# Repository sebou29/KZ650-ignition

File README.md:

# KZ650-ignition
KZ650 ignition arduino nano

Arduino nano ignition for four stroke engine motorcycle (KZ650) 
Inspired by aepl and aecp
Optimized for kickstarter

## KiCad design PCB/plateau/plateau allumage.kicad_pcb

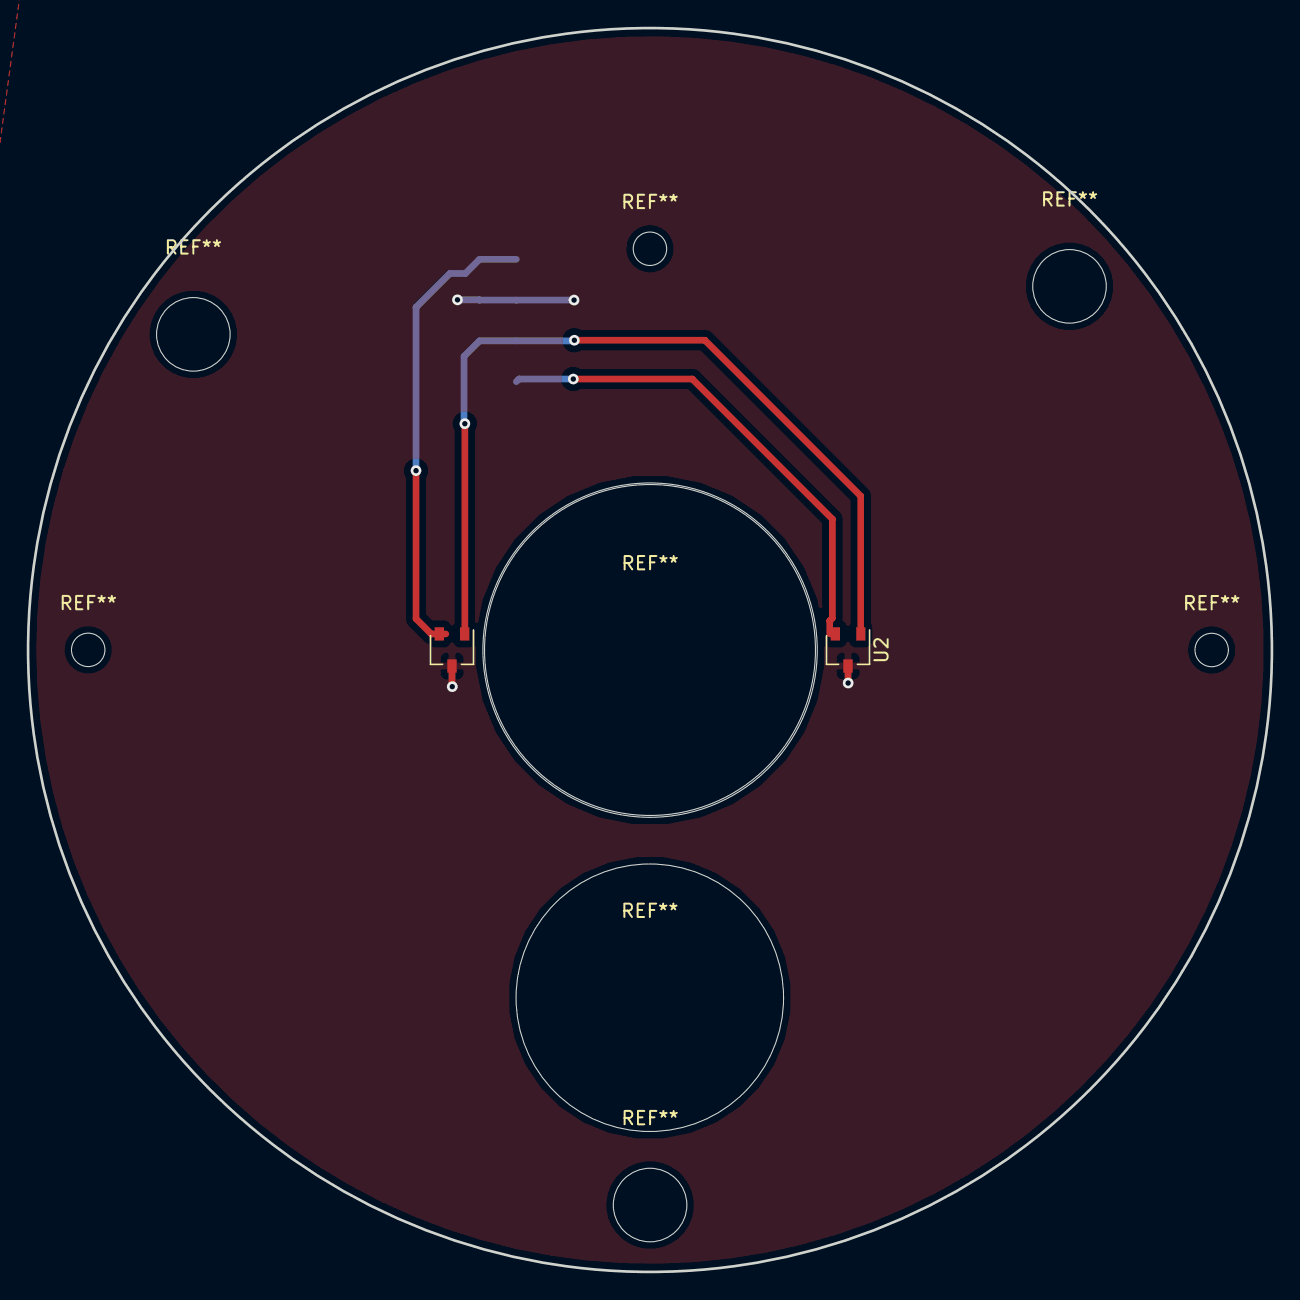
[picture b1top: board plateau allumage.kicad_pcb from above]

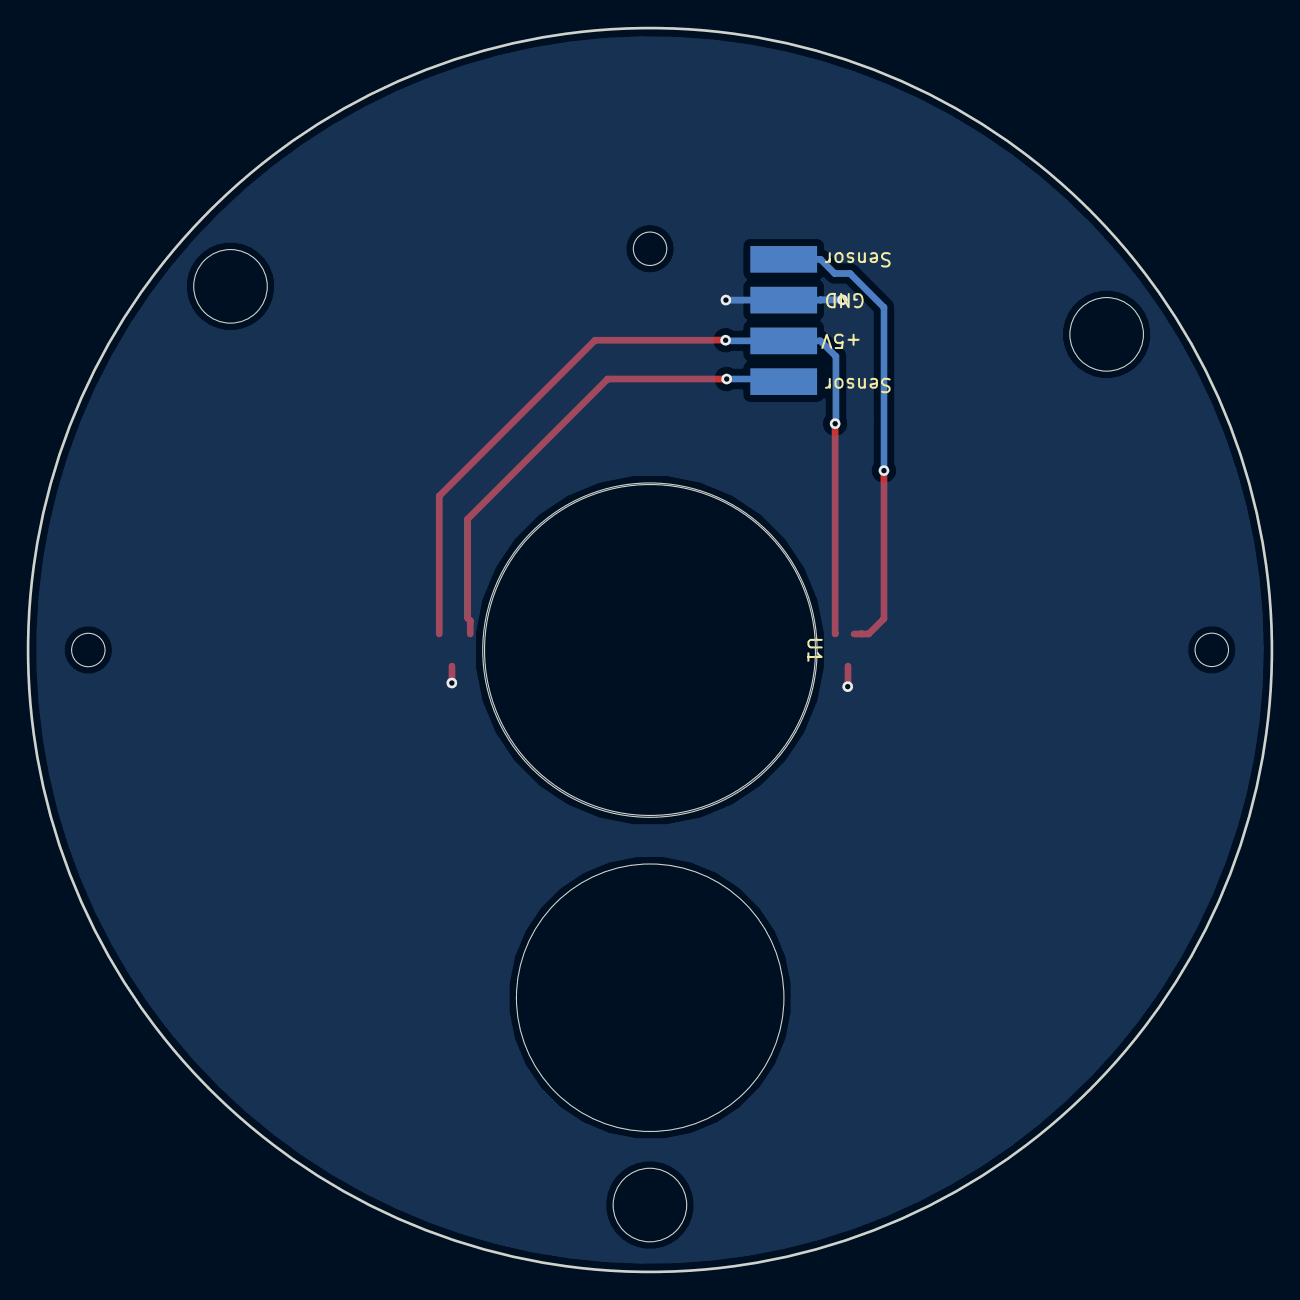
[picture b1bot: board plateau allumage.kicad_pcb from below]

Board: 2 copper layers, 93.0 x 93.0 mm, 6 parts (3 on the bottom side), 4 nets.

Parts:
+5V: MountingHole_Pad; SolderWirePad_1x01_SMD_5x10mm
GND: MountingHole_Pad; SolderWirePad_1x01_SMD_5x10mm
Sensor: MountingHole_Pad; SolderWirePad_1x01_SMD_5x10mm
Sensor#2: MountingHole_Pad; SolderWirePad_1x01_SMD_5x10mm
U1, U2: A1302ELHLT-T; SOT-23W

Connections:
GND: GND.1, U1.3, U2.3
unnamed: +5V.1, U1.1, U2.1
unnamed: Sensor#2.1, U1.2
unnamed: Sensor.1, U2.2

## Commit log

2022-09-06 KZ650 ignition
    Creation repository
2022-09-06 MAJ commentaires
    MAJ commentaires
2022-09-06 MAJ composants
    MAJ composants
